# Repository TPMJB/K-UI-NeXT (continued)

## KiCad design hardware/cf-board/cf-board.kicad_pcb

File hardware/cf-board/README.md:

# CF board: CompactFlash inside the Dreamcast

**Rev 1, designed 2026-09-29. Not yet made or tried.** A small board that
puts a CompactFlash card on the GD-ROM drive's bus (the G1 ATA bus) as its
second device, inside the console. The GD-ROM drive stays the first
(master) device and keeps working. The card is the slave, as KallistiOS's
`g1ata` driver expects: "The GD-ROM drive should always be the master
device on the chain, but you can hook up a hard drive or some other device
as a slave" (`dc/g1ata.h`).

The [standalone storage development build](../../docs/storage-transports.md)
adds a G1 ATA slave path, including the independent Games reader. Both this
board and the new IDE/CF driver still need hardware validation. See
[the handoff](../../docs/HANDOFF.md) for the current software state. Fitting
the board alone should not change the console's ordinary boot behavior.

| Top (card side) | Underside |
| --- | --- |
|  |  |

- [Schematic (PDF)](docs/cf-board-schematic.pdf)
- [Fit template, print at 100 % (PDF)](docs/cf-board-fit-template.pdf)
- [Gerbers for the board house](fab/cf-board-gerbers.zip),
  [parts list](fab/cf-board-bom.csv),
  [part positions](fab/cf-board-positions.csv)

## What the photos of the VA1 board show

From the owner's photos of both sides, with a ruler, sent on 2026-09-28:

- **CN503, the drive connector, is surface-mounted:** two rows of 25 legs at
  1.0 mm spacing. The A legs (A1 to A25, as printed on the board) run along
  the side facing the middle of the board. The B legs run along the side
  facing the board edge. Nothing comes through to the underside, so the
  wires are soldered to these legs.
- **The underside, under CN503,** has a grid of round test pads and the
  33 ohm resistor arrays in the drive's lines (RA507 to RA515 and others).
  The test pads would be easier to solder to than the legs, but nothing
  printed says which signal each carries (see
  [Using the test pads](#using-the-test-pads-instead)).
- **SCI connector points:** R115, R140 (beside IC105) and CE113 are on the
  underside. R122 and RA101 are not yet found in the photos. These matter
  for the [SCI connector plan](../../docs/sci-connector.md), not this board.

## How it connects

Each pad on the board takes one wire from the CN503 leg of the same name:
pad A4 to leg A4, pad B11 to leg B11. The pads are labelled A1 to A21 and
B1 to B21 on top, and with their signals on the underside. The CN503 signal
names follow the [iceGDROM](https://github.com/zeldin/iceGDROM) riser
board, which plugs into the same connector.

| Leg / pad | Signal | CF pin | Leg / pad | Signal | CF pin |
| --- | --- | --- | --- | --- | --- |
| A1 | +3V3 | JP1 (card supply) | B1 | +3V3 | JP1 (card supply) |
| A2 | /RESET | 41 (/RESET) | B2 | (unused) | leave unwired |
| A3 | +5V | JP1 (card supply) | B3 | +5V | JP1 (card supply) |
| A4 | D7 | 6 (D7) | B4 | D6 | 5 (D6) |
| A5 | D8 | 47 (D8) | B5 | D9 | 48 (D9) |
| A6 | D5 | 4 (D5) | B6 | D4 | 3 (D4) |
| A7 | D10 | 49 (D10) | B7 | D11 | 27 (D11) |
| A8 | GND | ground | B8 | GND | ground |
| A9 | D3 | 2 (D3) | B9 | D2 | 23 (D2) |
| A10 | D12 | 28 (D12) | B10 | D13 | 29 (D13) |
| A11 | D1 | 22 (D1) | B11 | D0 | 21 (D0) |
| A12 | D14 | 30 (D14) | B12 | D15 | 31 (D15) |
| A13 | GND | ground | B13 | GND | ground |
| A14 | DMARQ | 43 (DMARQ) | B14 | /DIOW | 35 (/IOWR) |
| A15 | /DIOR | 34 (/IORD) | B15 | IORDY | 42 (IORDY) |
| A16 | /DMACK | 44 (/DMACK) | B16 | INTRQ | 37 (INTRQ) |
| A17 | (unused) | leave unwired | B17 | DA1 | 19 (A1) |
| A18 | GND | ground | B18 | GND | ground |
| A19 | DA0 | 20 (A0) | B19 | DA2 | 18 (A2) |
| A20 | /CS0 | 7 (/CS0) | B20 | /CS1 | 32 (/CS1) |
| A21 | GND | ground | B21 | GND | ground |

**Never wire A22 to A25 or B22 to B25.** They carry CD audio, ground and,
on A25 and B25, **+12 V**, which would destroy the card. A3 and B3 (+5 V)
are needed only if the card is ever switched to 5 V (JP1, below).

That is 28 signal wires, 2 for 3.3 V and 8 for ground. Wire every ground:
the grounds are the return path for the 16 data lines.

## Wiring it

1. **Check the connector's orientation first, with the console unplugged.**
   Put a multimeter on continuity. Legs A21 and B21 must beep to ground
   (the metal shield, or the shell of the AV connector). Leg A5 must not.
   Leg A1 must beep to leg B1 (both are 3.3 V). If the connector were turned
   end to end, A21 would be a data line and would not beep. If anything
   disagrees, stop and send a photo: the numbering differs from what this
   board expects.
2. Use thin insulated wire, such as 30 AWG wire-wrap wire, about 10 to 15 cm
   long and no longer than the chosen spot needs.
3. Tin each leg lightly, lay the wire on it, and touch it with a fine tip
   and flux. Keep solder off the connector's plastic and out of its
   opening. Lay the wires flat along the board so the GD-ROM drive still
   seats fully in CN503.
4. Solder the other end of each wire to the pad of the same name.
5. Before powering: check continuity from each leg to its pad; check that
   no two neighbouring legs are bridged, in both rows; and check there is
   no short between C1's two ends (the card supply and ground).

## Before and at first power-up

- **JP1** (underside) comes bridged between 1 and 2: the card runs from
  3.3 V. To run it from 5 V instead, cut the thin trace between pads 1 and 2
  and bridge 2 and 3. Stay on 3.3 V unless a measurement says otherwise
  (see the design notes).
- **JP2** (underside) stays open: the card is the slave. Bridging it makes
  the card the master, for trying the board on a PC's IDE port only.
- Fit a CompactFlash card. Any size will do; True IDE mode is part of every
  CF card.
- Power up with the drive connected. The console must start and read discs
  exactly as before. The ACT LED (underside) lights briefly at start-up as
  the card announces itself, and later while the card is busy.

## Making it

- **Board:** 2 layers, 1.6 mm, 66.5 x 54 mm, any colour. Upload
  [cf-board-gerbers.zip](fab/cf-board-gerbers.zip). It fits the standard
  service of the usual board houses: 0.25 mm tracks, 0.2 mm spacing,
  0.3 mm drills. Choose **ENIG** (gold) plating if offered: its flat pads
  make the socket's 0.635 mm pins easier to solder by hand.
- **Parts:** [cf-board-bom.csv](fab/cf-board-bom.csv). The socket is a 3M
  N7E50-E516PG-30 CompactFlash header. The rest are 0805 resistors,
  capacitors and an LED.
- **Order of soldering:** the CF socket first (flux, tack two corner pins,
  drag-solder the rest, then check every gap with a magnifier), then the
  underside parts. The wire pads get their wires last, at the console.

## Where it goes

The board with a card fitted is about 7 mm thick in all, and the card
slides in from the right-hand edge. Print the
[fit template](docs/cf-board-fit-template.pdf) at 100 %, check that its bar
measures 50 mm, cut out the outline, and try it inside the console with
the drive and the power supply fitted. Double-sided foam tape holds it; the
two M2 holes also take nylon screws, and tracks stay 2.4 mm clear of them.
If no spot fits, the outline can change: the whole design is regenerated
from [tools/design.py](tools/design.py).

## Using the test pads instead

The round pads on the underside under CN503 are probably test points for
the same signals, which would make easier solder points. That is not
confirmed. To use them: with the board out and unplugged, beep from each
CN503 leg (top side) to the test pads (underside), write down the pad for
each signal in a copy of the table above, and send the list for checking
before soldering. Any signal without a test pad is wired at its leg.

## Design notes

- **3.3 V card supply.** The iceGDROM emulator drives these lines straight
  from a 3.3 V chip, so the Dreamcast's side works at 3.3 V. The GD-ROM
  drive's own output level is not documented. If it drove 5 V onto the bus,
  a card running at 3.3 V would be stressed. JP1 allows 5 V operation, as
  the iceGDROM riser's slave connector does. The level can be settled by
  measuring a data line while the drive reads a disc, before a card goes in.
- **The row names agree.** On the iceGDROM riser, the A row and the A25
  end face the riser's body, which lies over the middle of the mainboard,
  where the drive sits. That matches VA1's silkscreen, with A1 to A25 along
  the side of CN503 facing the middle of the board. The orientation check
  in the wiring steps catches a connector turned end to end.
- **No series resistors** on the board. The Dreamcast already has 33 ohm
  resistors in these lines. With short wires and a single card, the board
  stays simple, like the usual IDE modification.
- **No master/slave handshake with the drive.** The drive connector carries
  neither DASP nor PDIAG. The card's DASP line drives the ACT LED, and
  PDIAG has its own pull-up.
- **True IDE mode:** ATA SEL (pin 9) and A3 to A10 are grounded, and WE
  (pin 36) is held high. CSEL (pin 39) is left open, so the card is the
  slave. The CF pin assignments were checked against published True IDE
  tables.
- **The socket's footprint** is KiCad's `CF-Card_3M_N7E50-E516xx-30`, with
  the copper rings of its two unconnected board-lock holes cut from 3.99 to
  3.2 mm, so that they clear the locating holes by 0.55 mm instead of
  0.155 mm (`cf-board.pretty`).

## Files and checks

- `cf-board.kicad_pro`, `.kicad_sch`, `.kicad_pcb`: the KiCad 7 project.
  `cf-board.kicad_sym` holds the socket's symbol, and `cf-board.pretty` its
  footprint.
- `tools/design.py`: the connector pinouts, the parts and every
  connection, in one place. `tools/build.sh` rebuilds everything from it:
  schematic, netlist check, placement, autorouting with Freerouting 1.9,
  ground pours and stitching, DRC, and the files in `fab/` and `docs/`.
- `tools/check_netlist.py` compares KiCad's netlist, from the schematic and
  again from the finished board, with `design.py`. It stands in for ERC,
  which KiCad 7's command line lacks. `tools/drc.py` runs KiCad's DRC.

For rev 1, both netlist checks found 36 nets, 102 connections and no
problems. The DRC found no violations and no unconnected pads, and every
footprint matches its library.

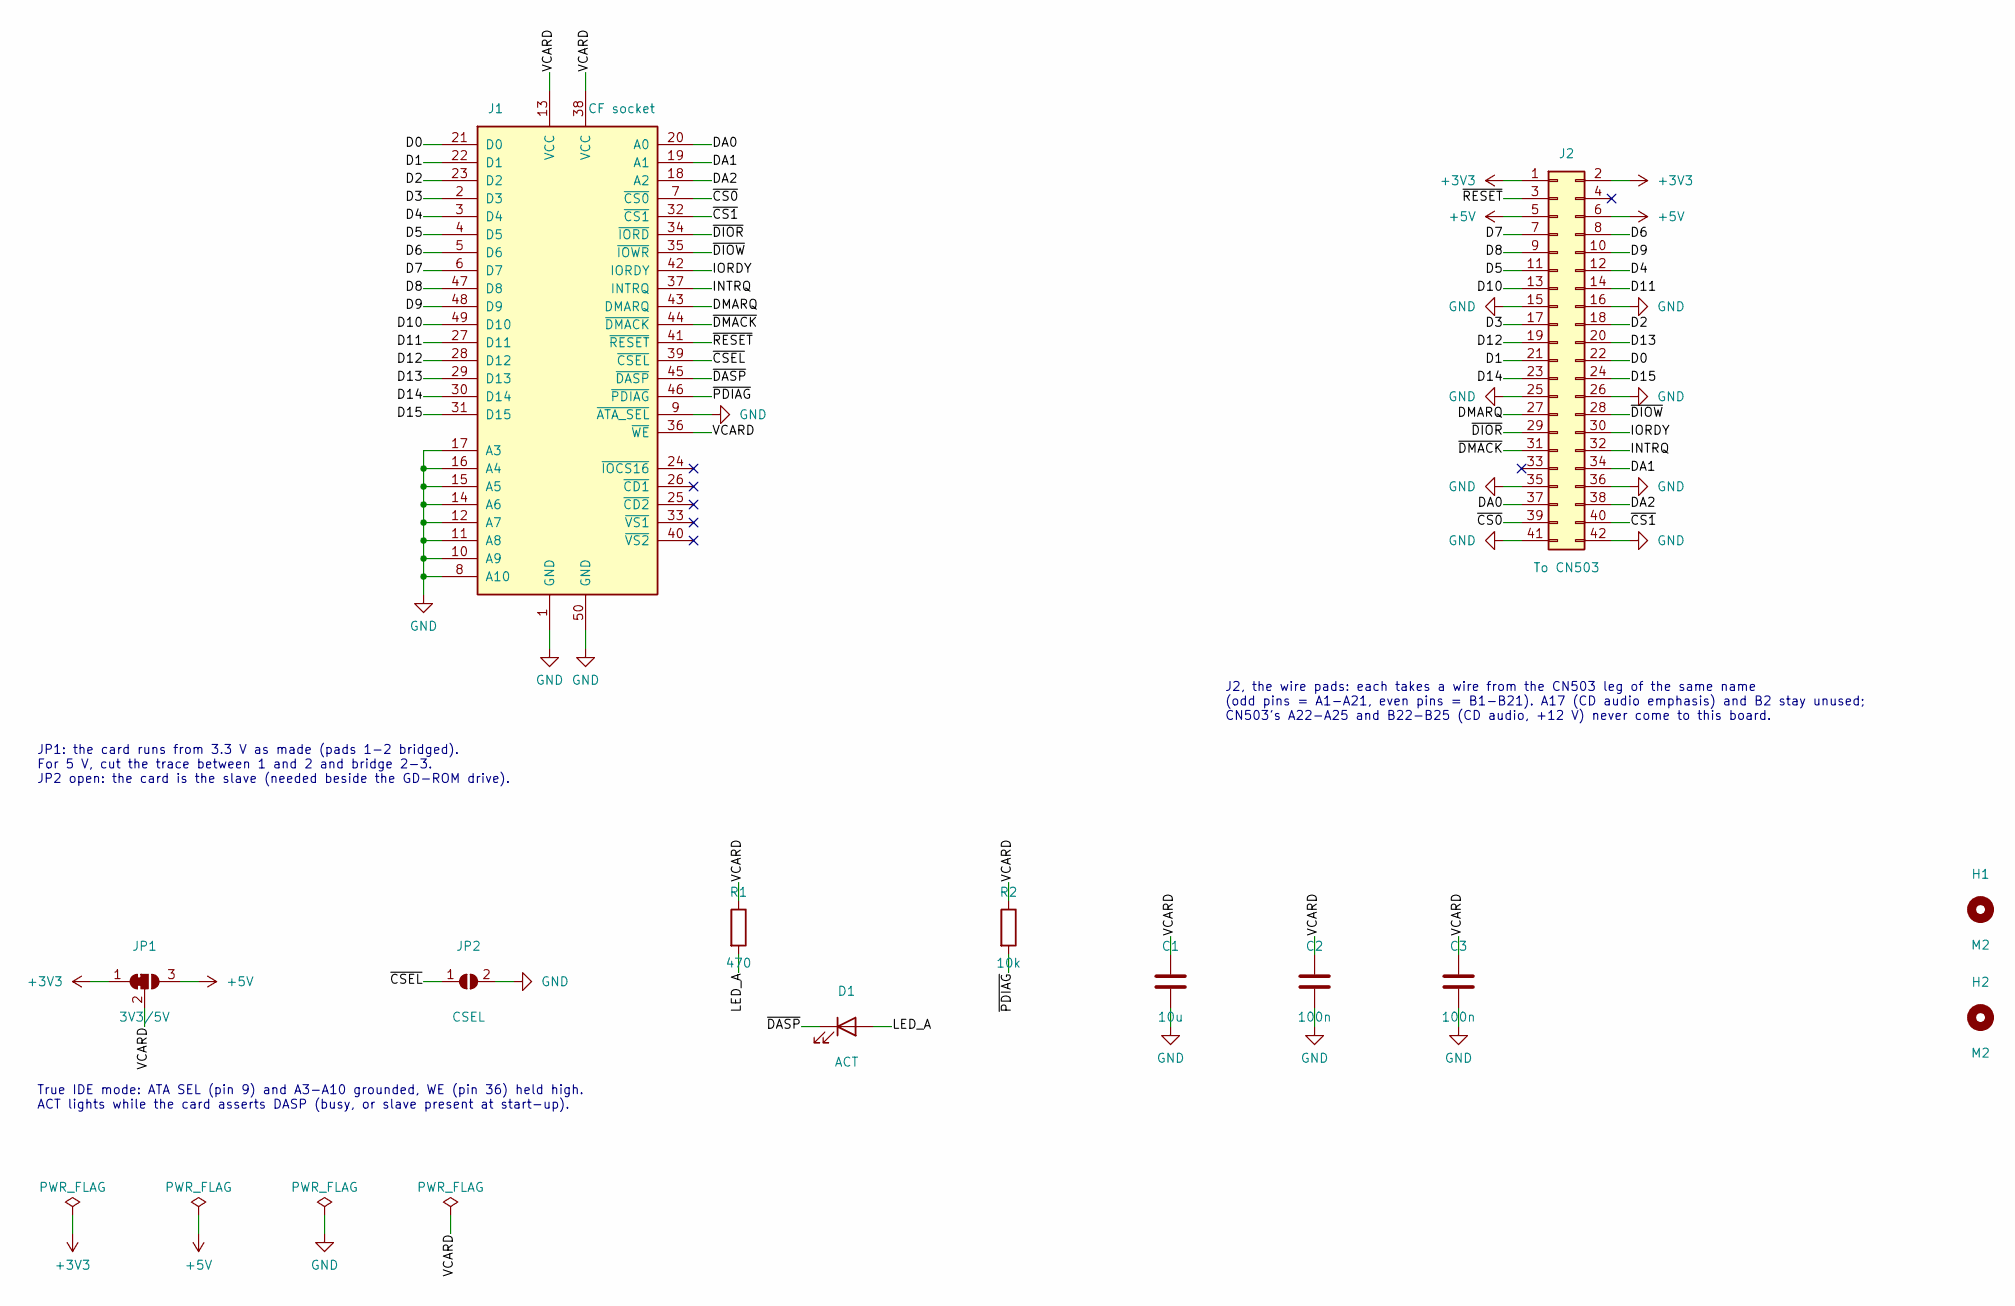
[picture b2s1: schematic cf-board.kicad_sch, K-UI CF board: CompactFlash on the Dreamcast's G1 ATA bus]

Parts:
C1: 10u; C_0805_2012Metric_Pad1.18x1.45mm_HandSolder
C2, C3: 100n; C_0805_2012Metric_Pad1.18x1.45mm_HandSolder
D1: ACT; LED_0805_2012Metric_Pad1.15x1.40mm_HandSolder
H1, H2: M2; MountingHole_2.2mm_M2
J1: CF socket; CF-Card_3M_N7E50-E516xx-30_SmallRing
J2: To CN503; PinHeader_2x21_P2.00mm_Vertical
JP1: 3V3/5V; SolderJumper-3_P1.3mm_Bridged12_RoundedPad1.0x1.5mm
JP2: CSEL; SolderJumper-2_P1.3mm_Open_RoundedPad1.0x1.5mm
R1: 470; R_0805_2012Metric_Pad1.20x1.40mm_HandSolder
R2: 10k; R_0805_2012Metric_Pad1.20x1.40mm_HandSolder

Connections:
+3V3: J2.1, J2.2, JP1.1 (A)
+5V: J2.5, J2.6, JP1.3 (B)
/D0: J1.21 (D0), J2.22
/D1: J1.22 (D1), J2.21
/D2: J1.23 (D2), J2.18
/D3: J1.2 (D3), J2.17
/D4: J1.3 (D4), J2.12
/D5: J1.4 (D5), J2.11
/D6: J1.5 (D6), J2.8
/D7: J1.6 (D7), J2.7
/D8: J1.47 (D8), J2.9
/D9: J1.48 (D9), J2.10
/D10: J1.49 (D10), J2.13
/D11: J1.27 (D11), J2.14
/D12: J1.28 (D12), J2.19
/D13: J1.29 (D13), J2.20
/D14: J1.30 (D14), J2.23
/D15: J1.31 (D15), J2.24
/DA0: J1.20 (A0), J2.37
/DA1: J1.19 (A1), J2.34
/DA2: J1.18 (A2), J2.38
/DMARQ: J1.43 (DMARQ), J2.27
/INTRQ: J1.37 (INTRQ), J2.32
/IORDY: J1.42 (IORDY), J2.30
/LED_A: D1.2 (A), R1.2
/VCARD: C1.1, C2.1, C3.1, J1.13 (VCC), J1.36 (~WE), J1.38 (VCC), JP1.2 (C), R1.1, R2.1
/~CS0: J1.7 (~CS0), J2.39
/~CS1: J1.32 (~CS1), J2.40
/~CSEL: J1.39 (~CSEL), JP2.1 (A)
/~DASP: D1.1 (K), J1.45 (~DASP)
/~DIOR: J1.34 (~IORD), J2.29
/~DIOW: J1.35 (~IOWR), J2.28
/~DMACK: J1.44 (~DMACK), J2.31
/~PDIAG: J1.46 (~PDIAG), R2.2
/~RESET: J1.41 (~RESET), J2.3
GND: C1.2, C2.2, C3.2, J1.1 (GND), J1.8 (A10), J1.9 (~ATA_SEL), J1.10 (A9), J1.11 (A8), J1.12 (A7), J1.14 (A6), J1.15 (A5), J1.16 (A4), J1.17 (A3), J1.50 (GND), J2.15, J2.16, J2.25, J2.26, J2.35, J2.36, J2.41, J2.42, JP2.2 (B)

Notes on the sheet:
J2, the wire pads: each takes a wire from the CN503 leg of the same name (odd pins = A1-A21, even pins = B1-B21). A17 (CD audio emphasis) and B2 stay unused; CN503's A22-A25 and B22-B25 (CD audio, +12 V) never come to this board.
JP1: the card runs from 3.3 V as made (pads 1-2 bridged). For 5 V, cut the trace between 1 and 2 and bridge 2-3. JP2 open: the card is the slave (needed beside the GD-ROM drive).
True IDE mode: ATA SEL (pin 9) and A3-A10 grounded, WE (pin 36) held high. ACT lights while the card asserts DASP (busy, or slave present at start-up).

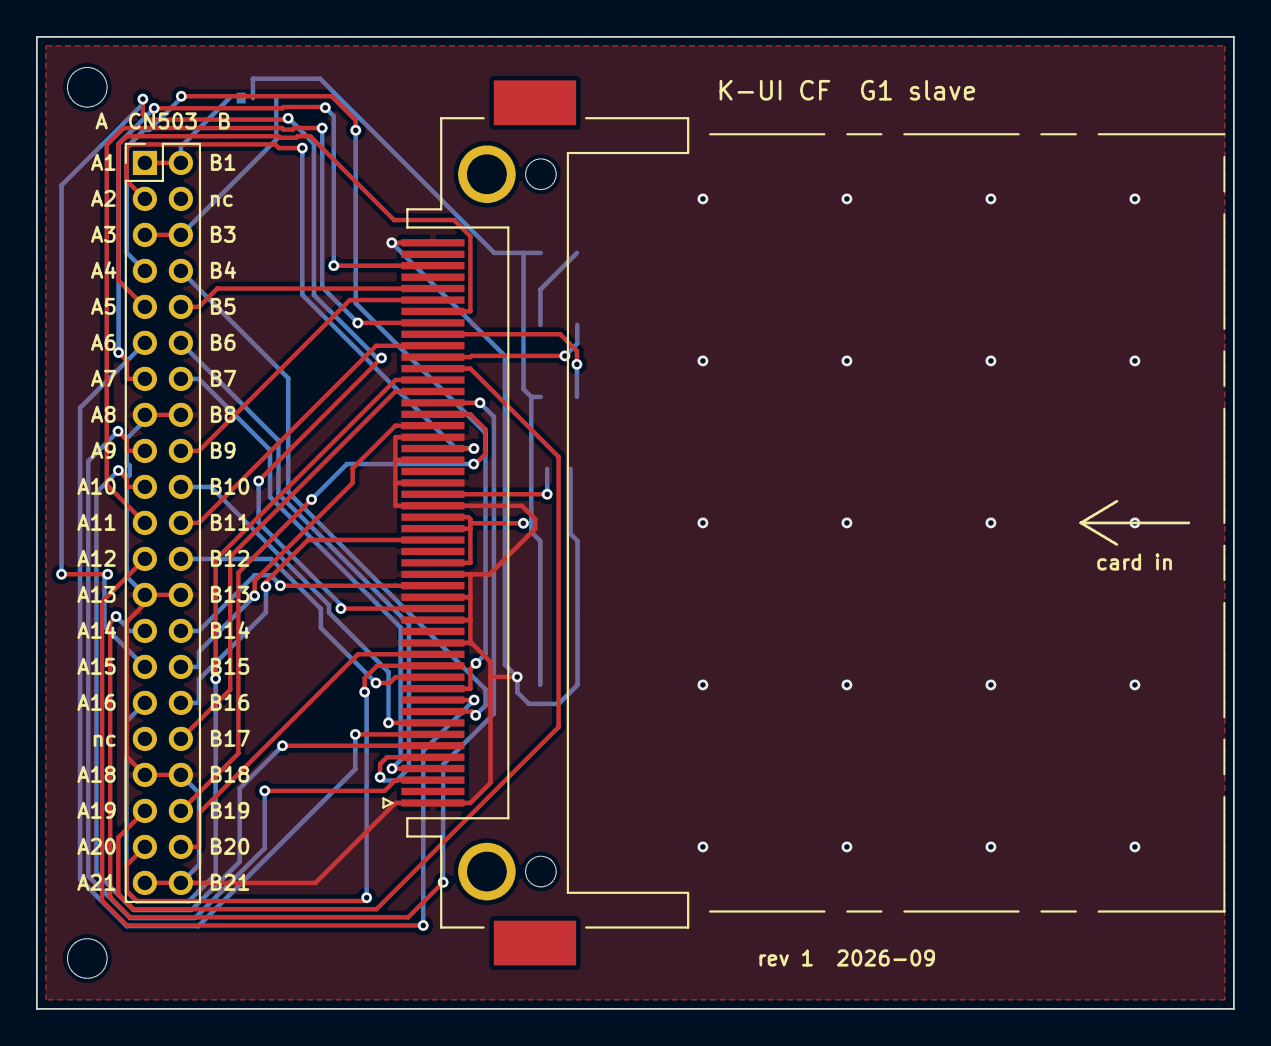
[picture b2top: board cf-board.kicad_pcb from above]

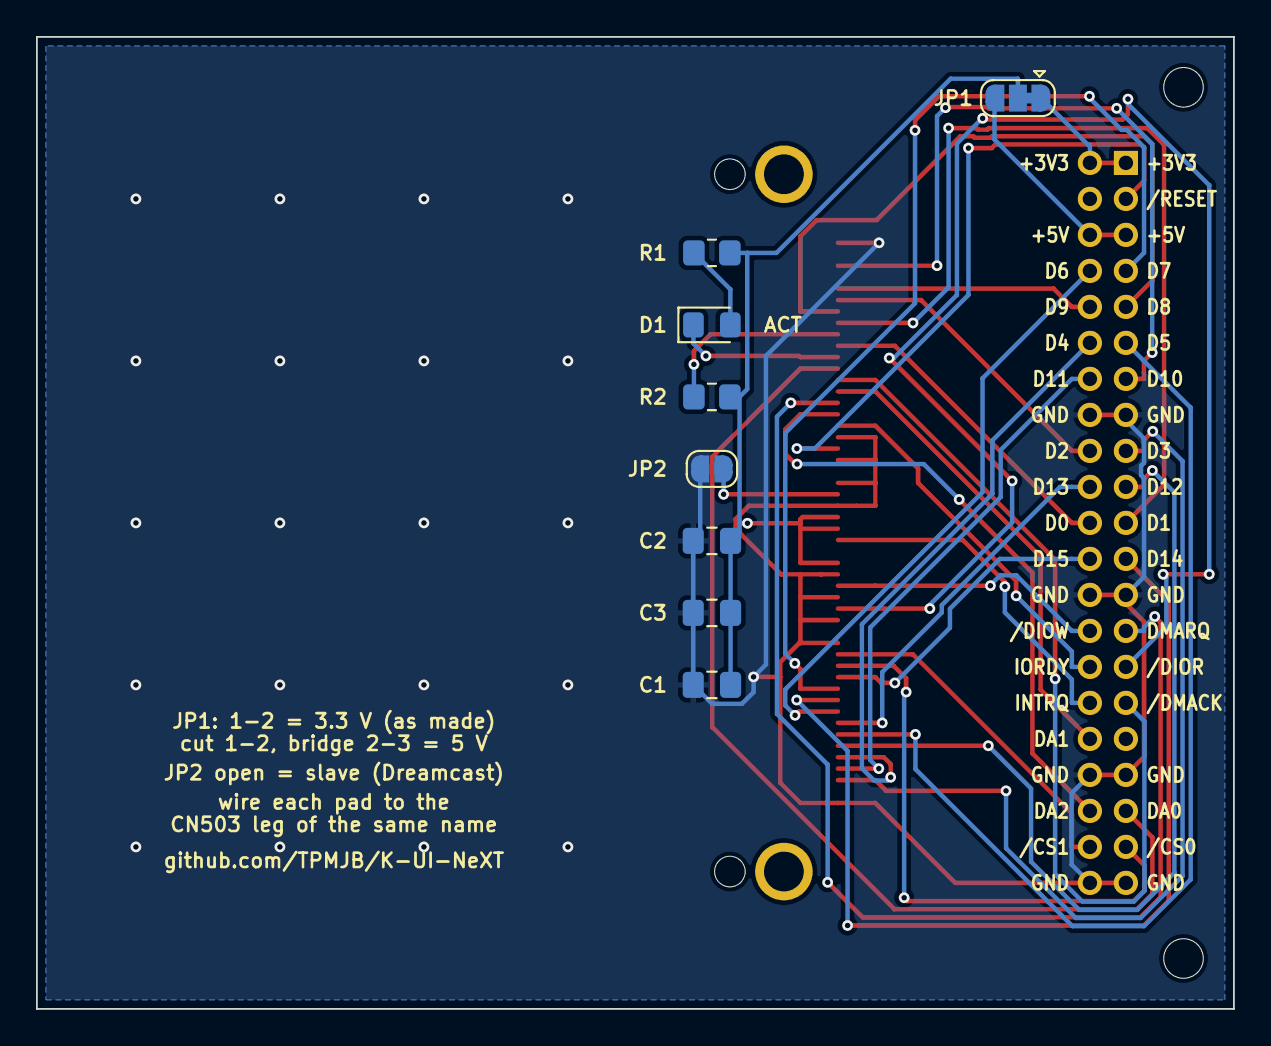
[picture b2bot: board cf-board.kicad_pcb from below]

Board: 2 copper layers, 66.5 x 54.0 mm, 12 parts (8 on the bottom side), 36 nets.

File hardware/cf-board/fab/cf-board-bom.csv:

References,Quantity,Value,Footprint,Description,Suggested part
C1,1,10u,Capacitor_SMD:C_0805_2012Metric_Pad1.18x1.45mm_HandSolder,"10 uF 16 V X5R, 0805",10 uF 16 V X5R 0805
C2 C3,2,100n,Capacitor_SMD:C_0805_2012Metric_Pad1.18x1.45mm_HandSolder,"100 nF X7R, 0805",100 nF 50 V X7R 0805
D1,1,ACT,LED_SMD:LED_0805_2012Metric_Pad1.15x1.40mm_HandSolder,"Activity LED, green, 0805",green LED 0805 (about 2 V at 2 mA)
H1 H2,2,M2,MountingHole:MountingHole_2.2mm_M2,Mounting hole,"nothing, or a nylon M2 screw"
J1,1,CF socket,cf-board:CF-Card_3M_N7E50-E516xx-30_SmallRing,"CompactFlash header, Type I, SMT, 3M N7E50-E516PG-30",3M N7E50-E516PG-30
J2,1,To CN503,Connector_PinHeader_2.00mm:PinHeader_2x21_P2.00mm_Vertical,"Wire pads, 2.0 mm grid (fit nothing, or a 2 x 21 2.0 mm header)","nothing (wires), or a 2 x 21 2.0 mm pin header"
JP1,1,3V3/5V,Jumper:SolderJumper-3_P1.3mm_Bridged12_RoundedPad1.0x1.5mm,Card supply: 3.3 V as made (cut the trace and bridge 2-3 for 5 V),nothing: solder jumper on the board
JP2,1,CSEL,Jumper:SolderJumper-2_P1.3mm_Open_RoundedPad1.0x1.5mm,Open: slave (as needed in the Dreamcast); bridged: master,nothing: solder jumper on the board
R1,1,470,Resistor_SMD:R_0805_2012Metric_Pad1.20x1.40mm_HandSolder,"Activity LED resistor, 0805",470 ohm 1% 0805
R2,1,10k,Resistor_SMD:R_0805_2012Metric_Pad1.20x1.40mm_HandSolder,"PDIAG pull-up, 0805",10 kohm 1% 0805
